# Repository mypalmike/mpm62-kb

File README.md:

# mpm62-kb
Schematics etc for split 62-key 60% keyboard.

Left side uses an arduino pro micro with left-side exit. Right side uses expander. Simple 4-pin connector carries i2c.

## Status

Currently in early stages.

* 2020-09-04 - Probably not final, but first potentially viable schematic.
* 2020-09-06 - Right-side (more complex) PCB routing complete.
* 2020-09-30 - (branch) Both sides updated for throughhole solder and expander to simplify wiring.

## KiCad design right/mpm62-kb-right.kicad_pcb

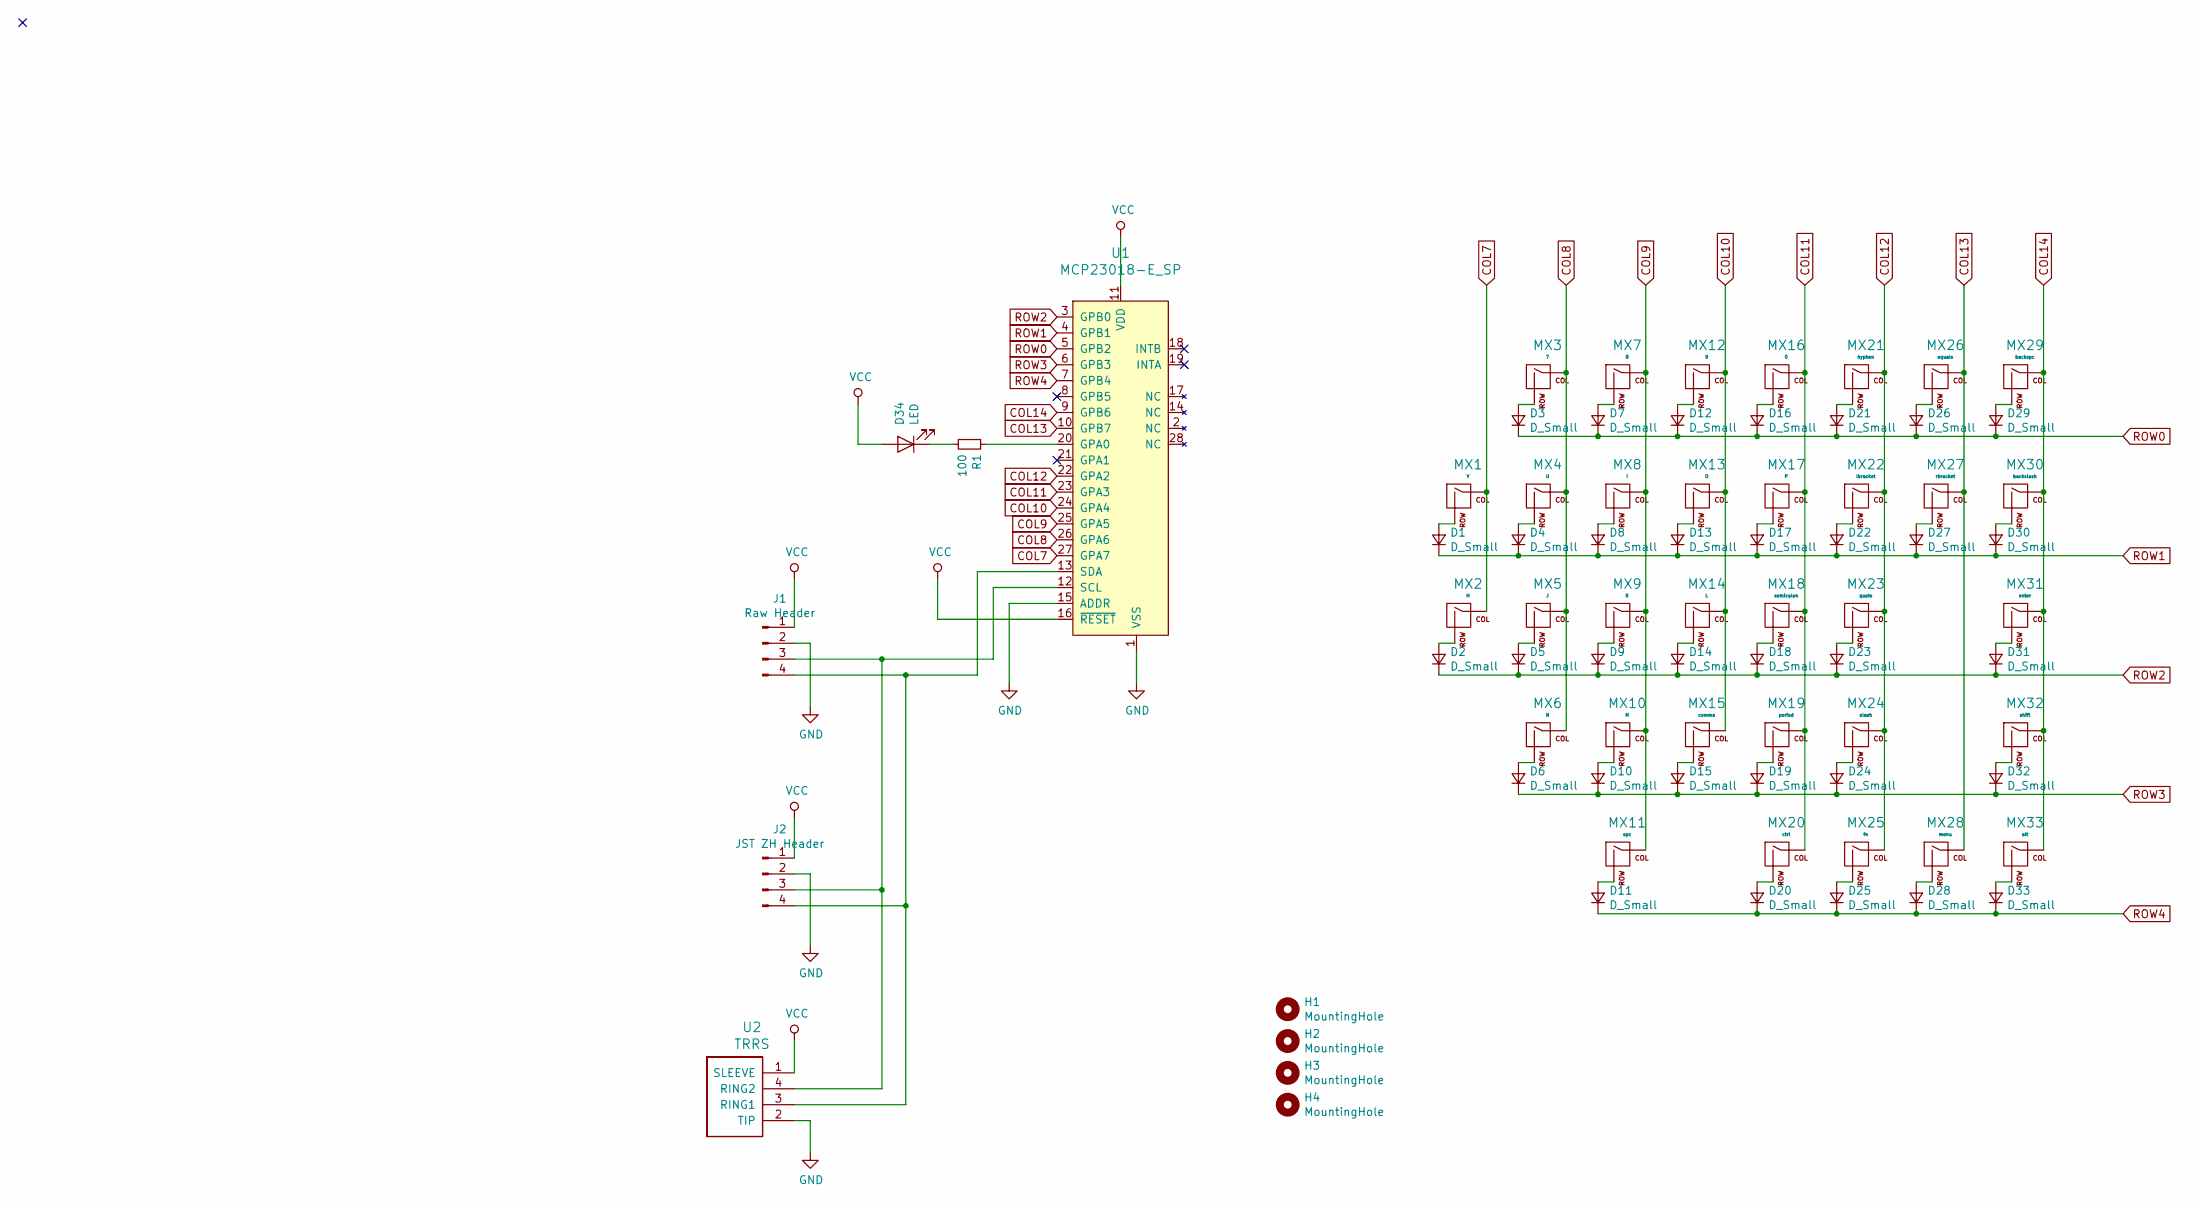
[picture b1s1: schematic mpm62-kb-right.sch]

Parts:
D1, D2, D3, D4, D5, D6, D7, D8, D9, D10, D11, D12, D13, D14, D15, D16, D17, D18, D19, D20, D21, D22, D23, D24, D25, D26, D27, D28, D29, D30, D31, D32, D33: D_Small; D_DO-35_SOD27_P7.62mm_Horizontal
D34: LED; LED_D3.0mm
H1, H2, H3, H4: MountingHole; MountingHole_2.2mm_M2_Pad
J1: Raw Header; PinHeader_1x04_P2.54mm_Vertical
J2: JST ZH Header; JST_ZH_B4B-ZR_1x04_P1.50mm_Vertical
MX1: Y; MXOnly-1U-NoLED
MX2: H; MXOnly-1U-NoLED
MX3: 7; MXOnly-1U-NoLED
MX4: U; MXOnly-1U-NoLED
MX5: J; MXOnly-1U-NoLED
MX6: N; MXOnly-1U-NoLED
MX7: 8; MXOnly-1U-NoLED
MX8: I; MXOnly-1U-NoLED
MX9: K; MXOnly-1U-NoLED
MX10: M; MXOnly-1U-NoLED
MX11: spc; MXOnly-3U-ReversedStabilizers-NoLED
MX12: 9; MXOnly-1U-NoLED
MX13: O; MXOnly-1U-NoLED
MX14: L; MXOnly-1U-NoLED
MX15: comma; MXOnly-1U-NoLED
MX16: 0; MXOnly-1U-NoLED
MX17: P; MXOnly-1U-NoLED
MX18: semicolon; MXOnly-1U-NoLED
MX19: period; MXOnly-1U-NoLED
MX20: ctrl; MXOnly-1.25U-NoLED
MX21: hyphen; MXOnly-1U-NoLED
MX22: lbracket; MXOnly-1U-NoLED
MX23: quote; MXOnly-1U-NoLED
MX24: slash; MXOnly-1U-NoLED
MX25: fn; MXOnly-1.25U-NoLED
MX26: equals; MXOnly-1U-NoLED
MX27: rbracket; MXOnly-1U-NoLED
MX28: menu; MXOnly-1.25U-NoLED
MX29: backspc; MXOnly-2U-NoLED
MX30: backslash; MXOnly-1.5U-NoLED
MX31: enter; MXOnly-2.25U-NoLED
MX32: shift; MXOnly-2.75U-NoLED
MX33: alt; MXOnly-1.25U-NoLED
R1: 100; R_Axial_DIN0207_L6.3mm_D2.5mm_P7.62mm_Horizontal
U1: MCP23018-E_SP; DIP-28_W7.62mm; MPN MCP23018-E/SP; Digi-Key_PN MCP23018-E/SP-ND
U2: TRRS; TRRS-PJ-320A

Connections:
COL7: MX1.1 (COL), MX2.1 (COL), U1.27 (GPA7)
COL8: MX3.1 (COL), MX4.1 (COL), MX5.1 (COL), MX6.1 (COL), U1.26 (GPA6)
COL9: MX7.1 (COL), MX8.1 (COL), MX9.1 (COL), MX10.1 (COL), MX11.1 (COL), U1.25 (GPA5)
COL10: MX12.1 (COL), MX13.1 (COL), MX14.1 (COL), MX15.1 (COL), U1.24 (GPA4)
COL11: MX16.1 (COL), MX17.1 (COL), MX18.1 (COL), MX19.1 (COL), MX20.1 (COL), U1.23 (GPA3)
COL12: MX21.1 (COL), MX22.1 (COL), MX23.1 (COL), MX24.1 (COL), MX25.1 (COL), U1.22 (GPA2)
COL13: MX26.1 (COL), MX27.1 (COL), MX28.1 (COL), U1.10 (GPB7)
COL14: MX29.1 (COL), MX30.1 (COL), MX31.1 (COL), MX32.1 (COL), MX33.1 (COL), U1.9 (GPB6)
GND: J1.2, J2.2, U1.1 (VSS), U1.15 (ADDR), U2.2 (TIP)
unnamed: D1.2 (A), MX1.2 (ROW)
unnamed: D2.2 (A), MX2.2 (ROW)
unnamed: D3.2 (A), MX3.2 (ROW)
unnamed: D4.2 (A), MX4.2 (ROW)
unnamed: D5.2 (A), MX5.2 (ROW)
unnamed: D6.2 (A), MX6.2 (ROW)
unnamed: D7.2 (A), MX7.2 (ROW)
unnamed: D8.2 (A), MX8.2 (ROW)
unnamed: D9.2 (A), MX9.2 (ROW)
unnamed: D10.2 (A), MX10.2 (ROW)
unnamed: D11.2 (A), MX11.2 (ROW)
unnamed: D12.2 (A), MX12.2 (ROW)
unnamed: D13.2 (A), MX13.2 (ROW)
unnamed: D14.2 (A), MX14.2 (ROW)
unnamed: D15.2 (A), MX15.2 (ROW)
unnamed: D16.2 (A), MX16.2 (ROW)
unnamed: D17.2 (A), MX17.2 (ROW)
unnamed: D18.2 (A), MX18.2 (ROW)
unnamed: D19.2 (A), MX19.2 (ROW)
unnamed: D20.2 (A), MX20.2 (ROW)
unnamed: D21.2 (A), MX21.2 (ROW)
unnamed: D22.2 (A), MX22.2 (ROW)
unnamed: D23.2 (A), MX23.2 (ROW)
unnamed: D24.2 (A), MX24.2 (ROW)
unnamed: D25.2 (A), MX25.2 (ROW)
unnamed: D26.2 (A), MX26.2 (ROW)
unnamed: D27.2 (A), MX27.2 (ROW)
unnamed: D28.2 (A), MX28.2 (ROW)
unnamed: D29.2 (A), MX29.2 (ROW)
unnamed: D30.2 (A), MX30.2 (ROW)
unnamed: D31.2 (A), MX31.2 (ROW)
unnamed: D32.2 (A), MX32.2 (ROW)
unnamed: D33.2 (A), MX33.2 (ROW)
unnamed: D34.1 (K), R1.2
unnamed: J1.3, J2.3, U1.12 (SCL), U2.4 (RING2)
unnamed: J1.4, J2.4, U1.13 (SDA), U2.3 (RING1)
unnamed: R1.1, U1.20 (GPA0)
ROW0: D3.1 (K), D7.1 (K), D12.1 (K), D16.1 (K), D21.1 (K), D26.1 (K), D29.1 (K), U1.5 (GPB2)
ROW1: D1.1 (K), D4.1 (K), D8.1 (K), D13.1 (K), D17.1 (K), D22.1 (K), D27.1 (K), D30.1 (K), U1.4 (GPB1)
ROW2: D2.1 (K), D5.1 (K), D9.1 (K), D14.1 (K), D18.1 (K), D23.1 (K), D31.1 (K), U1.3 (GPB0)
ROW3: D6.1 (K), D10.1 (K), D15.1 (K), D19.1 (K), D24.1 (K), D32.1 (K), U1.6 (GPB3)
ROW4: D11.1 (K), D20.1 (K), D25.1 (K), D28.1 (K), D33.1 (K), U1.7 (GPB4)
VCC: D34.2 (A), J1.1, J2.1, U1.11 (VDD), U1.16 (~RESET), U2.1 (SLEEVE)

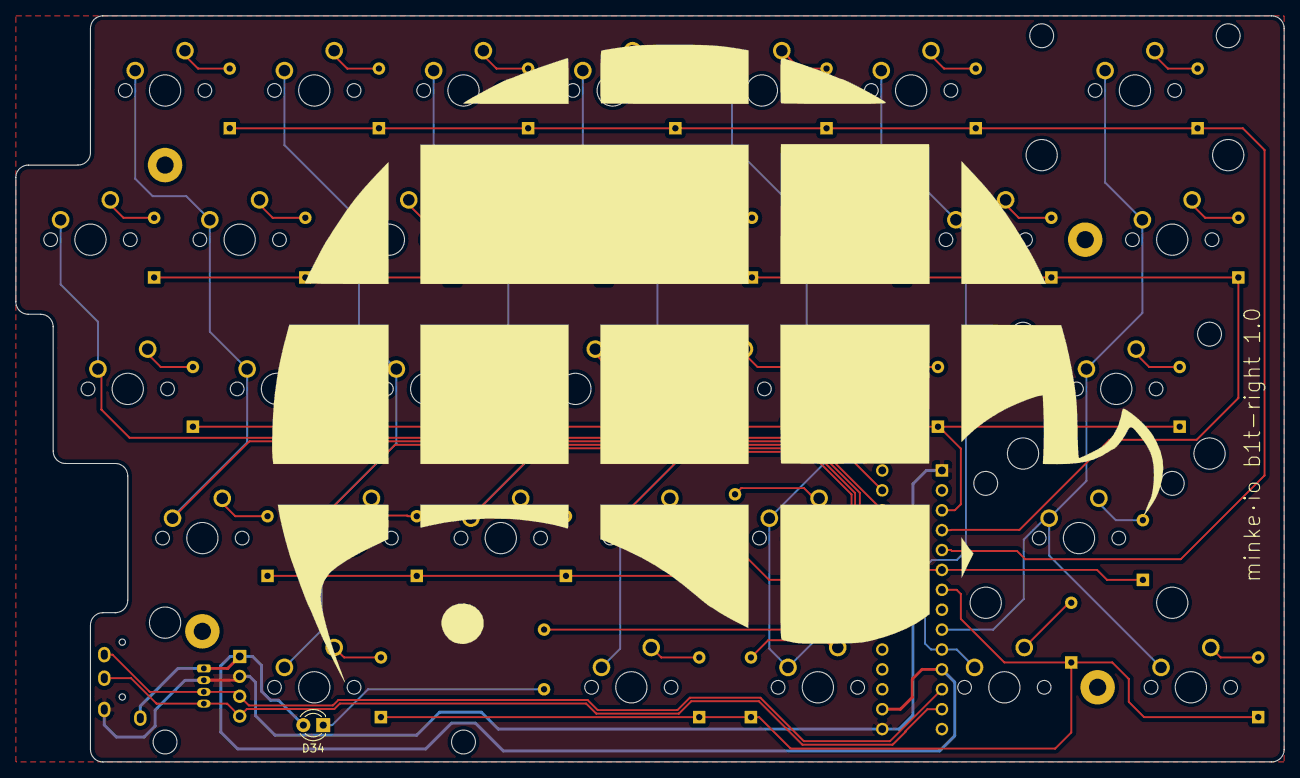
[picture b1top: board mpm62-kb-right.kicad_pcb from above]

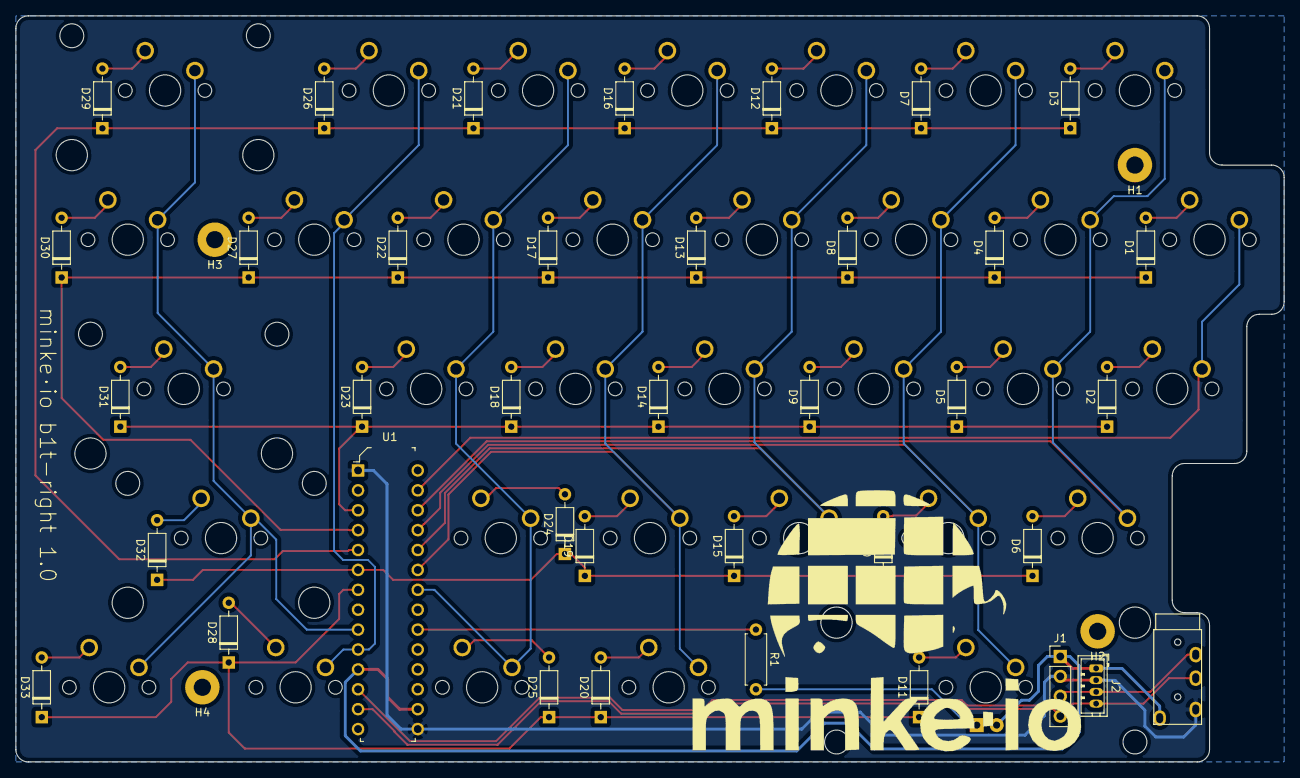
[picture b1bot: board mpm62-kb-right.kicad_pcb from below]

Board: 2 copper layers, 161.9 x 95.2 mm, 76 parts (42 on the bottom side), 52 nets.

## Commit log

2020-09-01 Initial empty project
2020-09-01 Add submodules
2020-09-01 just gitignore
2020-09-01 Configure local libs
2020-09-01 left schematic first pass
2020-09-01 Initial project for right
2020-09-01 Add cache schematic lib for left
2020-09-01 Add submodules right.
2020-09-01 Add libs to right
2020-09-01 Right MCU and switch layout.
2020-09-01 README status
2020-09-04 complete schematics for both left and right
2020-09-06 Add usb connector. Cleaned up crystal in schematic.
2020-09-06 Annotated components
2020-09-06 Assigned footprints
2020-09-06 Right pcb almost done.
2020-09-07 Minor pcb cleanup near crystal.
2020-09-07 Right pcb complete
2020-09-30 Schematic and pre-routed right-side based on mcp23018
2020-09-30 Fix resistor footprint, clean up layout.
2020-09-30 Finished right side routing, some simplification, ground fill.
2020-09-30 Add version text to front silk layer
2020-10-01 left side pcb components in place, not routed.
2020-10-01 Left side routed.
2020-10-01 left side ground filled and silk layer label
2020-10-01 Generated gerbers.
2020-10-01 Fix some small components in path of stabilizers.
2020-10-01 Generated right side gerber files.
2020-10-01 Minor config.
2020-10-28 Fix issues with left side: 1. SCL and SDA are swapped in the library file from github/ProMicroKiCad. Current fix is to swap the wires and mark the schematic to show which is which. Ultimately it woul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
2020-10-28 Fix issues on right side: 1. Remove reset switch and connect reset directly to vcc - switch was not useful and added complexity. 2. Inverted spacebar stabilizer holes (previous commit did not mention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
2021-01-08 nothing - cache commit
2021-03-27 Final for b1t (board 1 thruhole) board
